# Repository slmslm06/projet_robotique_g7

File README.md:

# projet_robotique_g7
Projet de robotique dépôts

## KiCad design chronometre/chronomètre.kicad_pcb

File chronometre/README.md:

Ce projet consiste en la conception et la réalisation d'un chronomètre électronique affichant le temps que prend le robot à traverser la section 8 sur des afficheurs 7 segments.
Le système repose sur des composants, notamment un générateur d'horloge à base de NE555, des compteurs CD4518 et des décodeurs CD4511 permettant de piloter les afficheurs.
Le projet a été conçu, simulé puis réalisé sur plaque labdec avant la création d'un circuit imprimé sous KiCad.

Fonctionnalités:
Génération d'une horloge à l'aide d'un NE555
Comptage des impulsions d'horloge
Affichage du comptage sur afficheurs 7 segments
Remise à zéro du chronomètre
Réalisation d'un circuit imprimé dédié

Technologies et outils utilisés:
Proteus (simulation)
KiCad (schéma et PCB)
Plaque Labdec (tests réels)

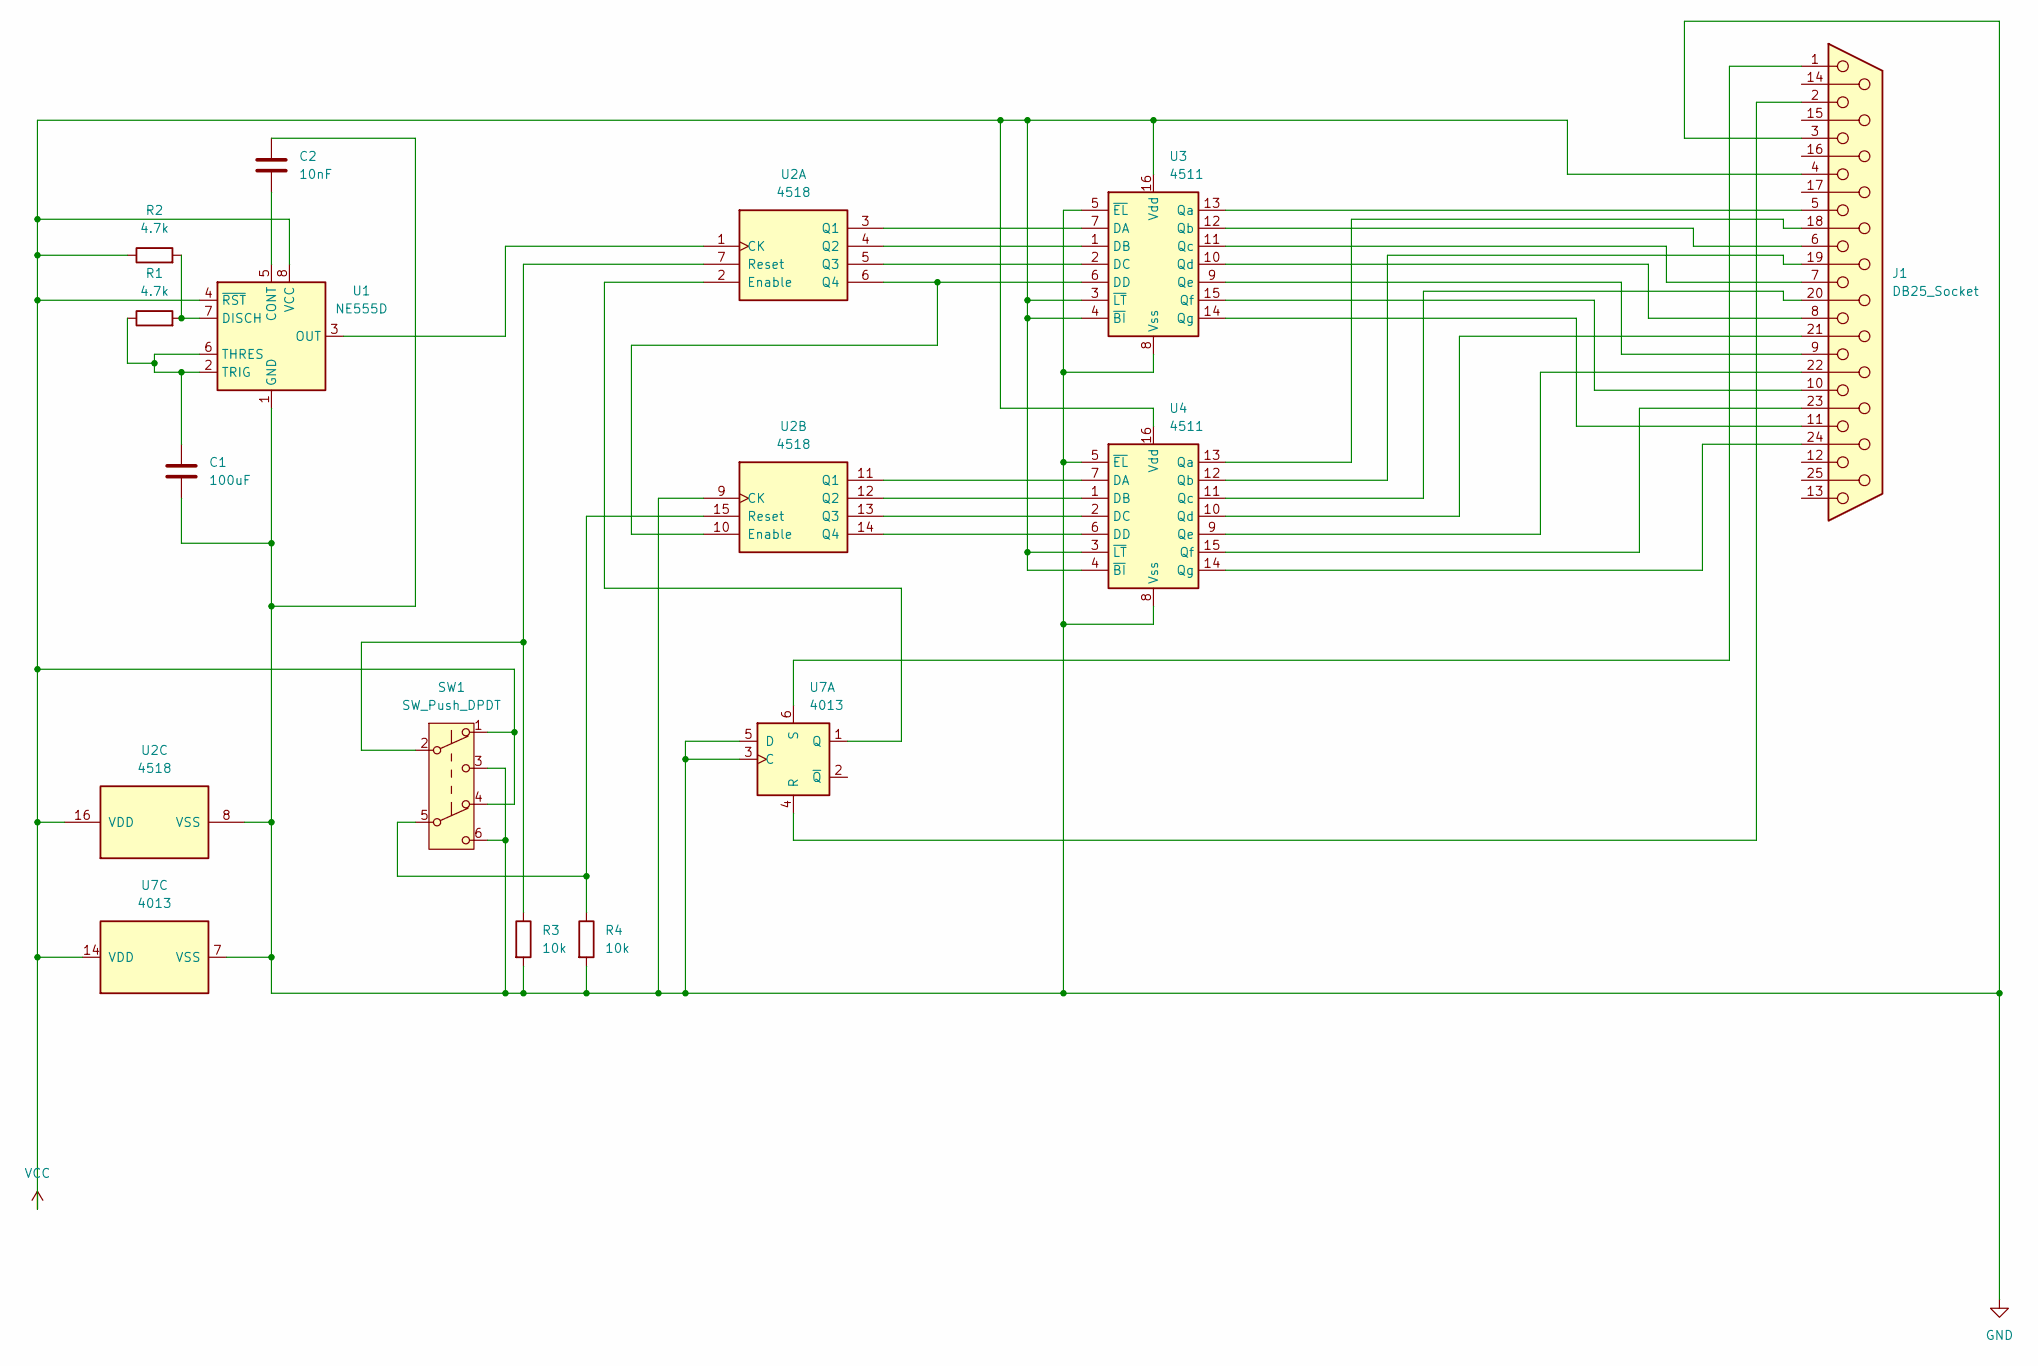
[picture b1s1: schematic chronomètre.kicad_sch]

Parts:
C1: 100uF; CP_Radial_D6.3mm_P2.50mm
C2: 10nF; C_Disc_D5.0mm_W2.5mm_P5.00mm
J1: DB25_Socket; DSUB-25_Socket_Horizontal_P2.77x2.84mm_EdgePinOffset9.40mm
R1, R2: 4.7k; R_Axial_DIN0207_L6.3mm_D2.5mm_P7.62mm_Horizontal
R3, R4: 10k; R_Axial_DIN0207_L6.3mm_D2.5mm_P7.62mm_Horizontal
SW1: SW_Push_DPDT; (footprint switch RS_734-7230
U1: NE555D; DIP-8_W7.62mm
U2: 4518
U3, U4: 4511; DIP-16_W7.62mm
U7: 4013

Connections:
GND: C1.2, C2.1, J1.3, R3.2, R4.2, SW1.3 (C), SW1.6 (C), U1.1 (GND), U2.8 (VSS), U2.9 (CK), U3.5 (~EL), U3.8 (Vss), U4.5 (~EL), U4.8 (Vss), U7.3 (C), U7.5 (D), U7.7 (VSS)
unnamed: J1.18, U4.13 (Qa)
unnamed: J1.19, U4.12 (Qb)
unnamed: J1.20, U4.11 (Qc)
unnamed: J1.21, U4.10 (Qd)
unnamed: J1.22, U4.9 (Qe)
unnamed: J1.23, U4.15 (Qf)
unnamed: J1.24, U4.14 (Qg)
unnamed: C2.2, U1.5 (CONT)
unnamed: R1.2, R2.2, U1.7 (DISCH)
unnamed: U1.3 (OUT), U2.1 (CK)
unnamed: C1.1, R1.1, U1.2 (TRIG), U1.6 (THRES)
unnamed: U2.2 (Enable), U7.1 (Q)
unnamed: U2.3 (Q1), U3.7 (DA)
unnamed: U2.4 (Q2), U3.1 (DB)
unnamed: U2.5 (Q3), U3.2 (DC)
unnamed: U2.6 (Q4), U2.10 (Enable), U3.6 (DD)
unnamed: R3.1, SW1.2 (B), U2.7 (Reset)
unnamed: U2.11 (Q1), U4.7 (DA)
unnamed: U2.12 (Q2), U4.1 (DB)
unnamed: U2.13 (Q3), U4.2 (DC)
unnamed: U2.14 (Q4), U4.6 (DD)
unnamed: R4.1, SW1.5 (B), U2.15 (Reset)
unnamed: J1.5, U3.13 (Qa)
unnamed: J1.6, U3.12 (Qb)
unnamed: J1.7, U3.11 (Qc)
unnamed: J1.8, U3.10 (Qd)
unnamed: J1.9, U3.9 (Qe)
unnamed: J1.10, U3.15 (Qf)
unnamed: J1.11, U3.14 (Qg)
unnamed: J1.2, U7.4 (R)
unnamed: J1.1, U7.6 (S)
VCC: J1.4, R2.1, SW1.1 (A), SW1.4 (A), U1.4 (~RST), U1.8 (VCC), U2.16 (VDD), U3.3 (~LT), U3.4 (~BI), U3.16 (Vdd), U4.3 (~LT), U4.4 (~BI), U4.16 (Vdd), U7.14 (VDD)

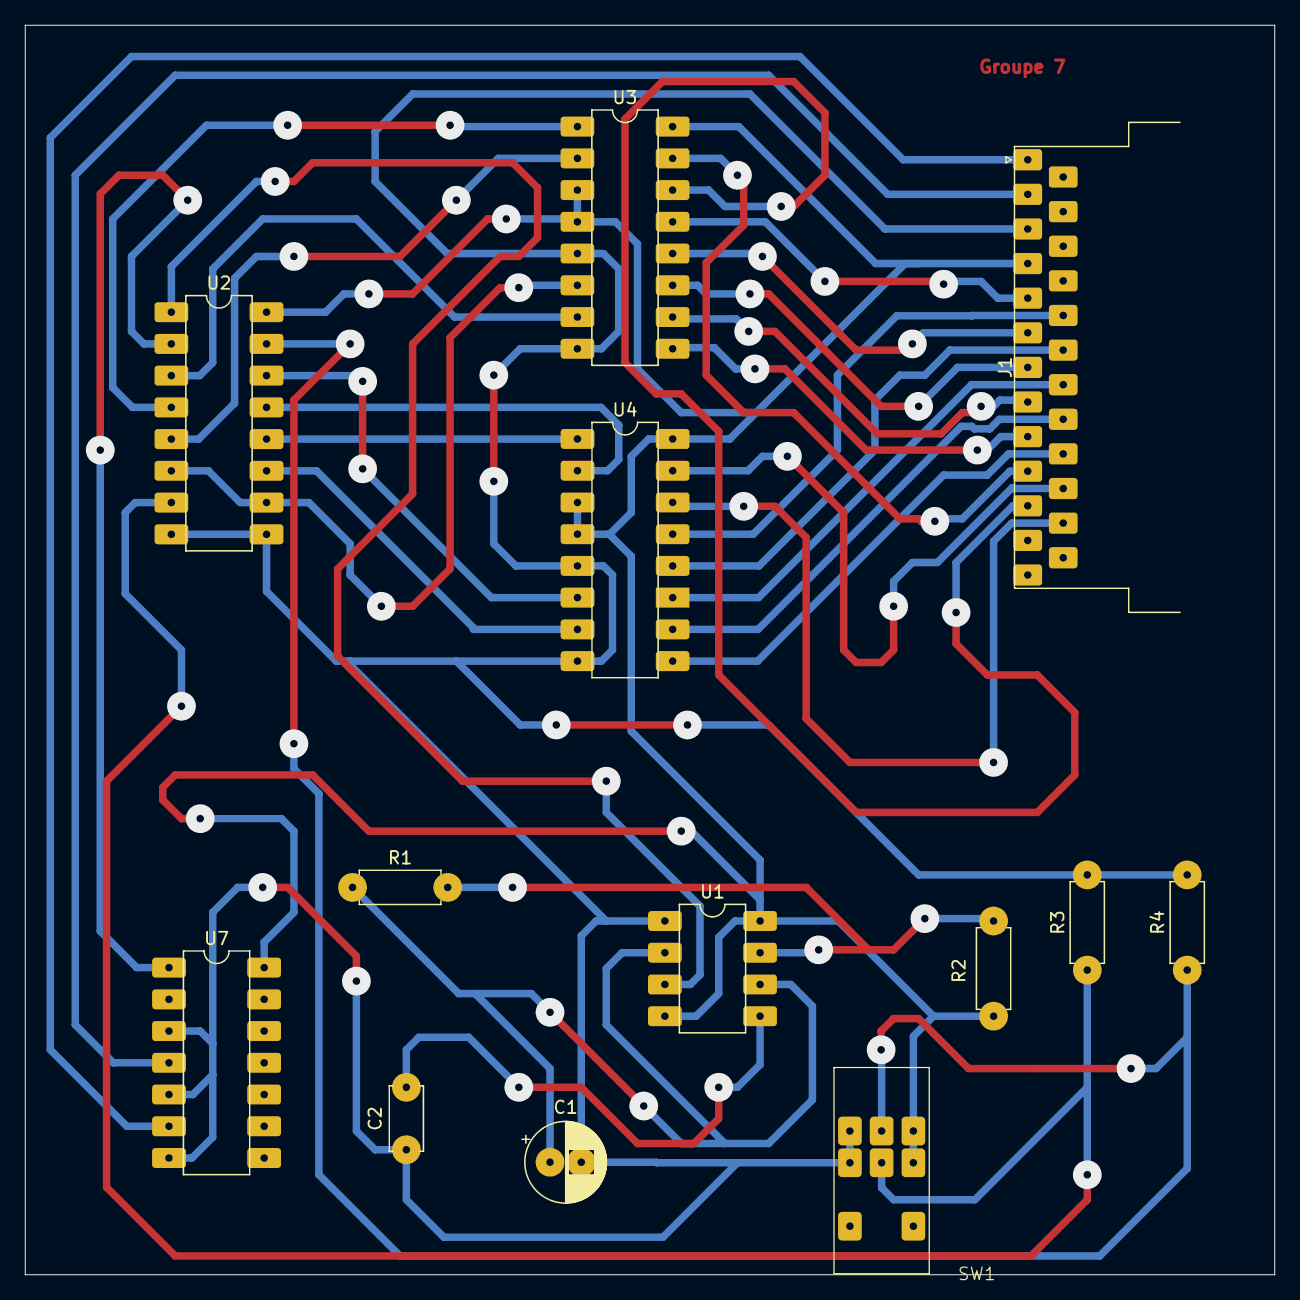
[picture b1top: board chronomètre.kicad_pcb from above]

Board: 2 copper layers, 100.0 x 100.0 mm, 13 parts (0 on the bottom side), 33 nets.

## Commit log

2026-05-27 Add file types to .gitignore
2026-05-28 Plan d'expérience du premier et second ordre
    Premier plan d'expérience avec comme variable, l'angle de tir et la vitesse
2026-05-28 Parcours v3 : arrêt ligne perpendiculaire + tunnel scan avant
    - Arrêt immédiat dès la détection d'une ligne 1111 (sans condition)
    - Évitement avec phase d'approche pour caler l'ultrason avant le longement
    - Tunnel : scan avant pour anticiper les murs, vitesse réduite
2026-05-28 Parcours v4 : freinage au premier 1111 + recherche de ligne centrée
    - Arrêt immédiat : premier 1111 = frein, confirmation pendant l'arrêt
    - Recherche de ligne qui s'arrête sur les capteurs du milieu
    - Tunnel : mesure ultrason avant en continu
2026-05-28 Parcours v5 : détection arrivée sortie d'évitement
    - Ligne perpendiculaire : freinage dès 3+ capteurs noirs (capte le passage rapide)
    - Évitement : retour direct en suivi de ligne dès que la ligne est revue
    - Tunnel : base v3 + scan rapide gauche/droite si mur devant
2026-05-28 Parcours v6 : tunnel en suivi de mur + arrivée évitement
    - Détection d'arrivée désactivée tant que le suivi normal n'a pas repris
    - Tunnel : suivi de mur (servo fixe d'un côté), plus fluide sur tunnel ondulé
2026-05-28 Parcours v7 : tunnel centré entre les murs + alignement post-évitement
    - Tunnel : scan avant à chaque cycle, suivi mur droit avec cible centrée
    - Évitement : pivot d'alignement final + drapeau post-évitement actif 5 s
2026-05-28 Parcours v8 : recentrage par pivot dans tunnel
    - Tunnel : pivot sur place avant chaque pas, puis avance droite
    - Évitement O1 : pivot 70° gauche après détection de la ligne
    - Évitement O2 : pivot 70° droite (alignement vers la rampe, pas vers V4)
2026-05-28 Parcours v9 : refonte du tunnel
    - Tunnel : mode urgent (pivot fort si mur latéral < 8 cm), servo à 135/45° pour capter les murs en biais, virage frontal corrigé
    - Évitement O1 : pivot final retiré (géré par le suivi de ligne)
    - Évitement O2 : pivot 70° droite conservé
2026-05-28 Parcours v10 : suivi de mur droit + intégration sections 5-6-7
    - Tunnel remplacé par un suivi du mur droit (correction proportionnelle)
    - Section 5 : montée rampe + suivi + approche du panneau
    - Section 6 : détection couleur + clignotement ruban LED 3 s
    - Section 7 : recul, demi-tour gauche, recherche de ligne
2026-05-28 Parcours v10.2 : tunnel+ évitement O1 en miroir d'O2
    - Tunnel : reprise exacte de code_tunnel.ino (cible 26 cm du mur droit)
    - O1 refait en miroir d'O2 (dépassement 35 cm + pivot 70° gauche final)
    - Post-évitement activé avant chercherLigne (évite un faux arrêt en arrivée)
    - Ajout du helper assurerServoAvant() en début de suivi de ligne
2026-05-28 Parcours v10.3 : entrée tunnel par timer + réglages évitement/servo
    - Détection entrée tunnel par timer 500 ms après perte de ligne (plus de détection d'obstacle frontal avant le tunnel : évite un faux O1)
    - O1 : distance de dépassement portée à 40 cm
    - Servo : délai de retour au centre allongé à 350-400 ms
2026-05-28 Parcours v_fiinale
    - Tunnel : version v10.3
    - Affichage LCD des sections
    - Séquence lanceur
    - Braquage fort adouci à VITESSE_BASE/3
2026-05-29 Create parcours_v3.ino
    - Arrêt immédiat dès la détection d'une ligne 1111 (sans condition)
    - Évitement avec phase d'approche pour caler l'ultrason avant le longement
    - Tunnel : scan avant pour anticiper les murs, vitesse réduite
2026-05-29 Parcours v5 : détection arrivée et sortie d'évitement
    - Ligne perpendiculaire : freinage dès 3+ capteurs noirs (capte le passage rapide)
    - Évitement : retour direct en suivi de ligne dès que la ligne est revue
    - Tunnel : base v3 (plus fiable) + scan rapide gauche/droite si mur devant
2026-05-29 Parcours v6 : tunnel en suivi de mur + arrivée après évitement
    - Détection d'arrivée désactivée tant que le suivi normal n'a pas repris
    - Tunnel : suivi de mur (servo fixe d'un côté), plus fluide sur tunnel ondulé
2026-05-29 Parcours v8 : recentrage par pivot systématique dans le tunnel
    - Tunnel : pivot sur place avant chaque pas, puis avance droite
    - Évitement O1 : pivot 70° gauche après détection de la ligne
    - Évitement O2 : pivot 70° droite (alignement vers la rampe, pas vers V4)
2026-05-29 Parcours v10.2 : tunnel+ évitement O1 en miroir d'O2
    - Tunnel : reprise de code_tunnel.ino (cible 26 cm du mur droit)
    - O1 refait en miroir d'O2 (dépassement 35 cm + pivot 70° gauche final)
    - Post-évitement activé avant chercherLigne (évite un faux arrêt en arrivée)
    - Ajout du helper assurerServoAvant() en début de suivi de ligne
2026-05-29 Parcours v10.3 : entrée tunnel par timer + réglages évitement/servo
    - Détection entrée tunnel par timer 500 ms après perte de ligne
    (plus de détection d'obstacle frontal avant le tunnel : évite un faux O1)
    - O1 : distance de dépassement portée à 40 cm
    - Servo : délai de retour au centre allongé à 350-400 ms
2026-05-29 Parcours final
    - Affichage LCD des sections
    - Séquence lanceur
    - Braquage fort adouci à VITESSE_BASE/3
2026-05-29 Enhance README with project overview and test results
    Added detailed project description and mechanical testing results for the passerelle model.
2026-05-29 Plan d'expérience et test README.md
2026-05-29 Phase finale de test
